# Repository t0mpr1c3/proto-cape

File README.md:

BeagleBone Black Proto Cape
===========================

This repository contains the Eagle design files for the LGX Proto Cape for the BeagleBone Black.  

Check out the LGX Proto Cape at http://www.logicsupply.com/products/cbb_proto

----

Follow us on Google+ for updates and more information: https://plus.google.com/u/0/b/103613886667848850929/

Created by Alexander Hiam for LGX / Logic Supply.

Creative Commons Attribution 3.0 Unported License.  
To view a copy of this license,visit http://creativecommons.org/licenses/by/3.0/.  
All text above must be included in any redistribution. 

Versions
--------

_PC01_

Magic Smoke logo applied to original LGX design.
Board truncated and SMD footprints removed.

_PC02_

Wider "wing" made narrower to match other side and allow access to header P6 on BeagleBone white.
Mounting holes added.
Adjustments to solder stop layer.

_PC03_

Swapped VDD5V and SYS5V labels on top silk layer.

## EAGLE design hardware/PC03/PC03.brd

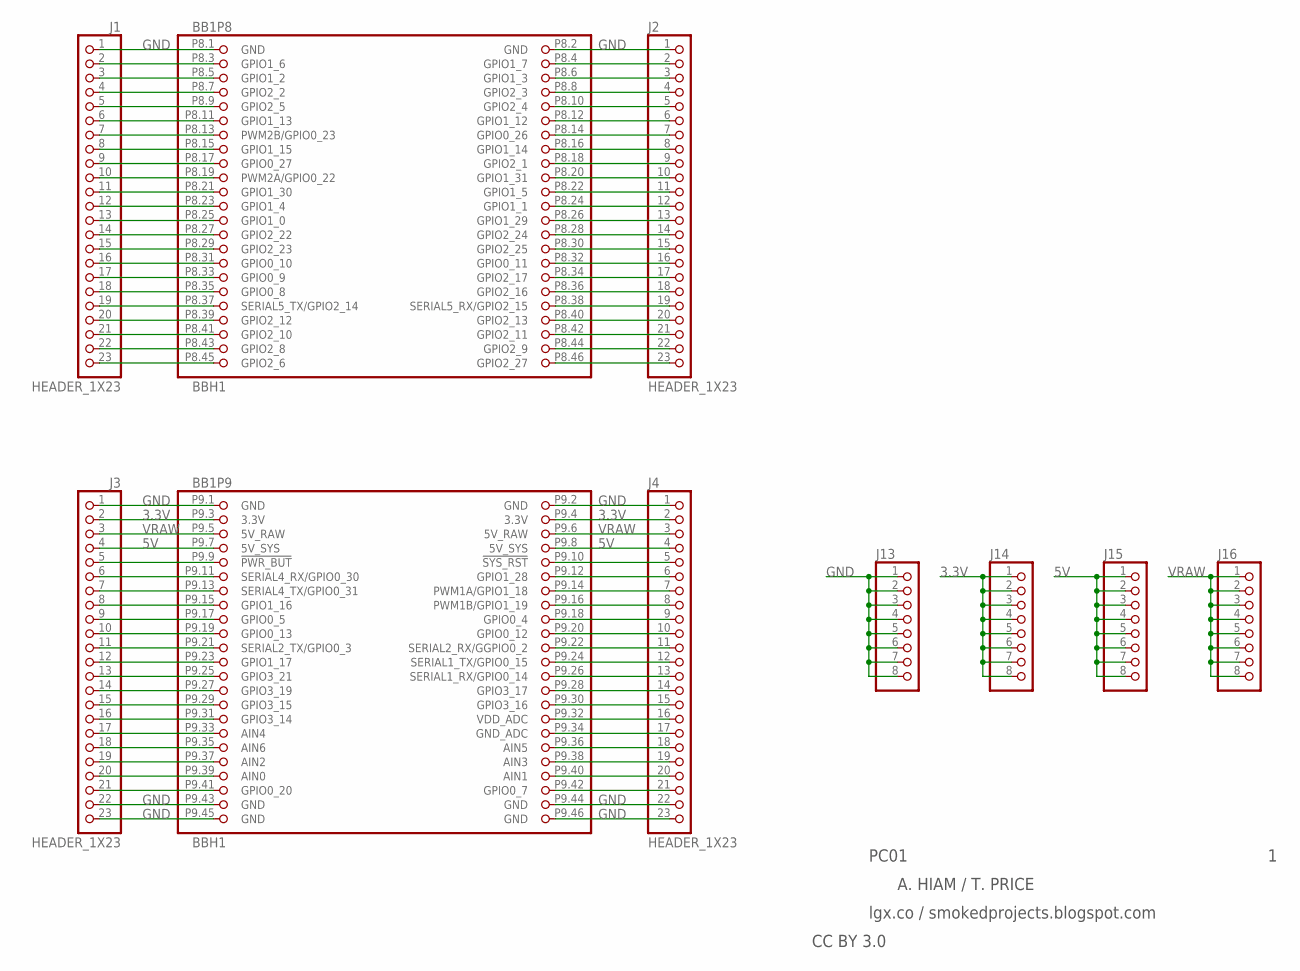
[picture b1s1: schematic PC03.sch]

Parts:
BB1: BBH1; BB_CAPE
J1, J2, J3, J4: HEADER_1X23
J13, J14, J15, J16: HEADER_1X8

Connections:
3.3V: BB1.P9.3 (3.3V), BB1.P9.4 (3.3V), J3.2, J4.2, J14.1, J14.2, J14.3, J14.4, J14.5, J14.6, J14.7, J14.8
5V: BB1.P9.7 (5V_SYS), BB1.P9.8 (5V_SYS), J3.4, J4.4, J15.1, J15.2, J15.3, J15.4, J15.5, J15.6, J15.7, J15.8
GND: BB1.P8.1 (GND), BB1.P8.2 (GND), BB1.P9.1 (GND), BB1.P9.2 (GND), BB1.P9.43 (GND), BB1.P9.44 (GND), BB1.P9.45 (GND), BB1.P9.46 (GND), J1.1, J2.1, J3.1, J3.22, J3.23, J4.1, J4.22, J4.23, J13.1, J13.2, J13.3, J13.4, J13.5, J13.6, J13.7, J13.8
unnamed: BB1.P8.4 (GPIO1_7), J2.2
unnamed: BB1.P8.6 (GPIO1_3), J2.3
unnamed: BB1.P8.8 (GPIO2_3), J2.4
unnamed: BB1.P8.10 (GPIO2_4), J2.5
unnamed: BB1.P8.12 (GPIO1_12), J2.6
unnamed: BB1.P8.14 (GPIO0_26), J2.7
unnamed: BB1.P8.16 (GPIO1_14), J2.8
unnamed: BB1.P8.18 (GPIO2_1), J2.9
unnamed: BB1.P8.20 (GPIO1_31), J2.10
unnamed: BB1.P8.22 (GPIO1_5), J2.11
unnamed: BB1.P8.24 (GPIO1_1), J2.12
unnamed: BB1.P8.26 (GPIO1_29), J2.13
unnamed: BB1.P8.28 (GPIO2_24), J2.14
unnamed: BB1.P8.30 (GPIO2_25), J2.15
unnamed: BB1.P8.32 (GPIO0_11), J2.16
unnamed: BB1.P8.34 (GPIO2_17), J2.17
unnamed: BB1.P8.36 (GPIO2_16), J2.18
unnamed: BB1.P8.38 (SERIAL5_RX/GPIO2_15), J2.19
unnamed: BB1.P8.40 (GPIO2_13), J2.20
unnamed: BB1.P8.42 (GPIO2_11), J2.21
unnamed: BB1.P8.44 (GPIO2_9), J2.22
unnamed: BB1.P8.46 (GPIO2_27), J2.23
unnamed: BB1.P8.45 (GPIO2_6), J1.23
unnamed: BB1.P8.43 (GPIO2_8), J1.22
unnamed: BB1.P8.41 (GPIO2_10), J1.21
unnamed: BB1.P8.39 (GPIO2_12), J1.20
unnamed: BB1.P8.37 (SERIAL5_TX/GPIO2_14), J1.19
unnamed: BB1.P8.35 (GPIO0_8), J1.18
unnamed: BB1.P8.33 (GPIO0_9), J1.17
unnamed: BB1.P8.31 (GPIO0_10), J1.16
unnamed: BB1.P8.29 (GPIO2_23), J1.15
unnamed: BB1.P8.27 (GPIO2_22), J1.14
unnamed: BB1.P8.25 (GPIO1_0), J1.13
unnamed: BB1.P8.23 (GPIO1_4), J1.12
unnamed: BB1.P8.21 (GPIO1_30), J1.11
unnamed: BB1.P8.19 (PWM2A/GPIO0_22), J1.10
unnamed: BB1.P8.17 (GPIO0_27), J1.9
unnamed: BB1.P8.15 (GPIO1_15), J1.8
unnamed: BB1.P8.13 (PWM2B/GPIO0_23), J1.7
unnamed: BB1.P8.11 (GPIO1_13), J1.6
unnamed: BB1.P8.9 (GPIO2_5), J1.5
unnamed: BB1.P8.7 (GPIO2_2), J1.4
unnamed: BB1.P8.5 (GPIO1_2), J1.3
unnamed: BB1.P8.3 (GPIO1_6), J1.2
unnamed: BB1.P9.41 (GPIO0_20), J3.21
unnamed: BB1.P9.39 (AIN0), J3.20
unnamed: BB1.P9.37 (AIN2), J3.19
unnamed: BB1.P9.35 (AIN6), J3.18
unnamed: BB1.P9.33 (AIN4), J3.17
unnamed: BB1.P9.31 (GPIO3_14), J3.16
unnamed: BB1.P9.29 (GPIO3_15), J3.15
unnamed: BB1.P9.27 (GPIO3_19), J3.14
unnamed: BB1.P9.25 (GPIO3_21), J3.13
unnamed: BB1.P9.23 (GPIO1_17), J3.12
unnamed: BB1.P9.21 (SERIAL2_TX/GPIO0_3), J3.11
unnamed: BB1.P9.19 (GPIO0_13), J3.10
unnamed: BB1.P9.17 (GPIO0_5), J3.9
unnamed: BB1.P9.15 (GPIO1_16), J3.8
unnamed: BB1.P9.13 (SERIAL4_TX/GPIO0_31), J3.7
unnamed: BB1.P9.11 (SERIAL4_RX/GPIO0_30), J3.6
unnamed: BB1.P9.9 (!PWR_BUT), J3.5
unnamed: BB1.P9.10 (!SYS_RST), J4.5
unnamed: BB1.P9.12 (GPIO1_28), J4.6
unnamed: BB1.P9.14 (PWM1A/GPIO1_18), J4.7
unnamed: BB1.P9.16 (PWM1B/GPIO1_19), J4.8
unnamed: BB1.P9.18 (GPIO0_4), J4.9
unnamed: BB1.P9.20 (GPIO0_12), J4.10
unnamed: BB1.P9.22 (SERIAL2_RX/GGPIO0_2), J4.11
unnamed: BB1.P9.24 (SERIAL1_TX/GPIO0_15), J4.12
unnamed: BB1.P9.26 (SERIAL1_RX/GPIO0_14), J4.13
unnamed: BB1.P9.28 (GPIO3_17), J4.14
unnamed: BB1.P9.30 (GPIO3_16), J4.15
unnamed: BB1.P9.32 (VDD_ADC), J4.16
unnamed: BB1.P9.34 (GND_ADC), J4.17
unnamed: BB1.P9.36 (AIN5), J4.18
unnamed: BB1.P9.38 (AIN3), J4.19
unnamed: BB1.P9.40 (AIN1), J4.20
unnamed: BB1.P9.42 (GPIO0_7), J4.21
VRAW: BB1.P9.5 (5V_RAW), BB1.P9.6 (5V_RAW), J3.3, J4.3, J16.1, J16.2, J16.3, J16.4, J16.5, J16.6, J16.7, J16.8

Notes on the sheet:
A. HIAM / T. PRICE
PC01
lgx.co / smokedprojects.blogspot.com
CC BY 3.0

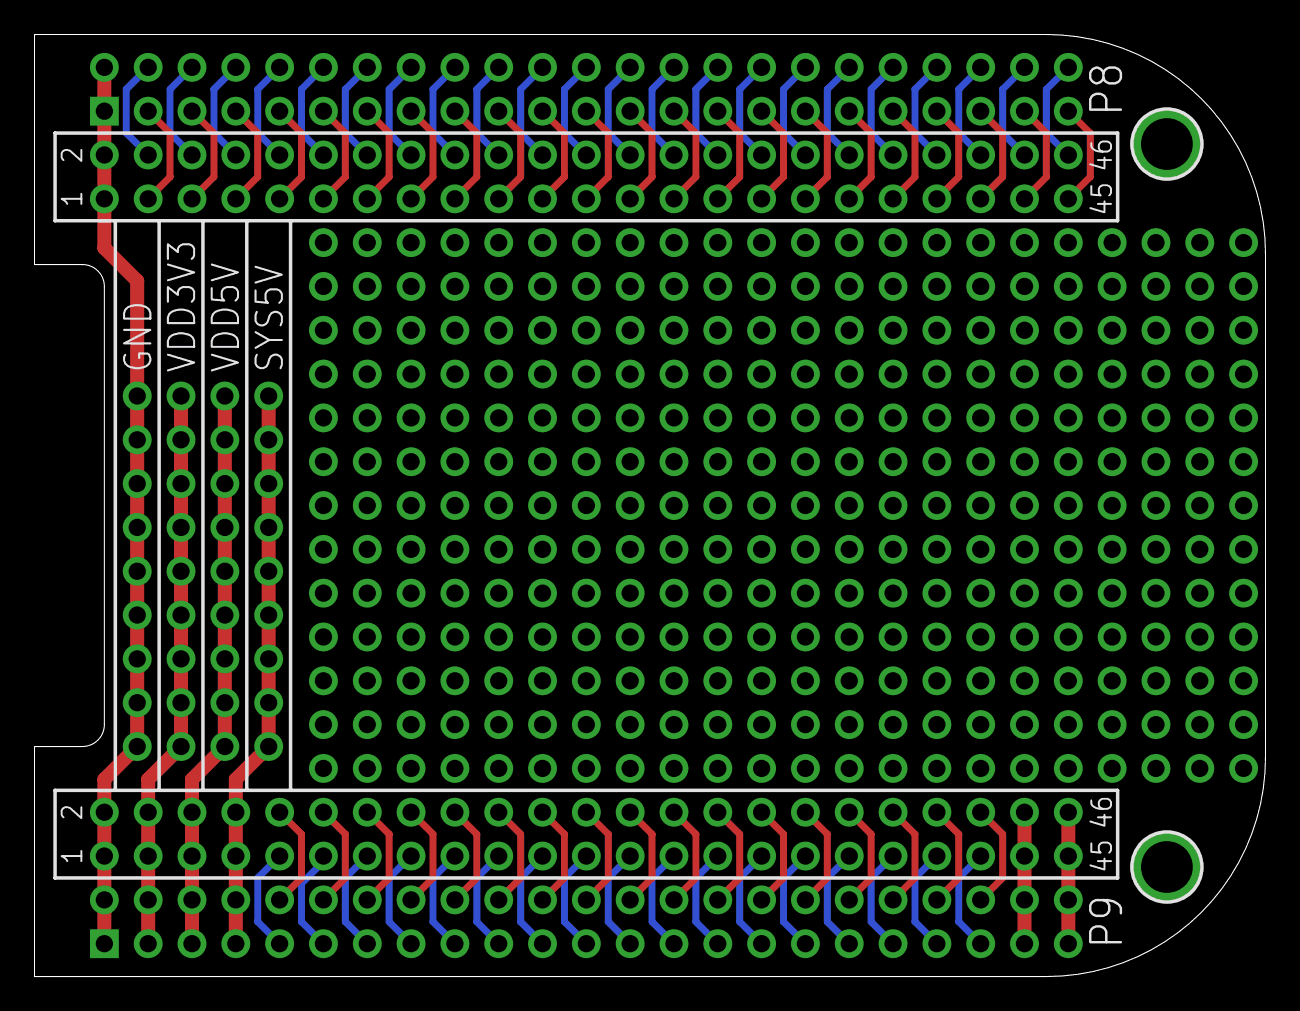
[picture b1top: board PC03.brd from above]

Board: 2 copper layers, 71.4 x 54.6 mm, 11 parts (0 on the bottom side), 82 nets.

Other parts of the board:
U$1, U$3: MOUNTINGHOLE_3.0_PLATEDTHIN

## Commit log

2014-01-21 Version PC01
2014-02-25 PC02 first draft
2014-02-25 added 2 mounting holes
2014-05-15 Version PC02
2021-08-25 PC03 commit

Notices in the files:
parts and their libraries:
microbuilder: This work is placed in the public domain, and may be freely used for commercial and non-commercial work with the following conditions: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
